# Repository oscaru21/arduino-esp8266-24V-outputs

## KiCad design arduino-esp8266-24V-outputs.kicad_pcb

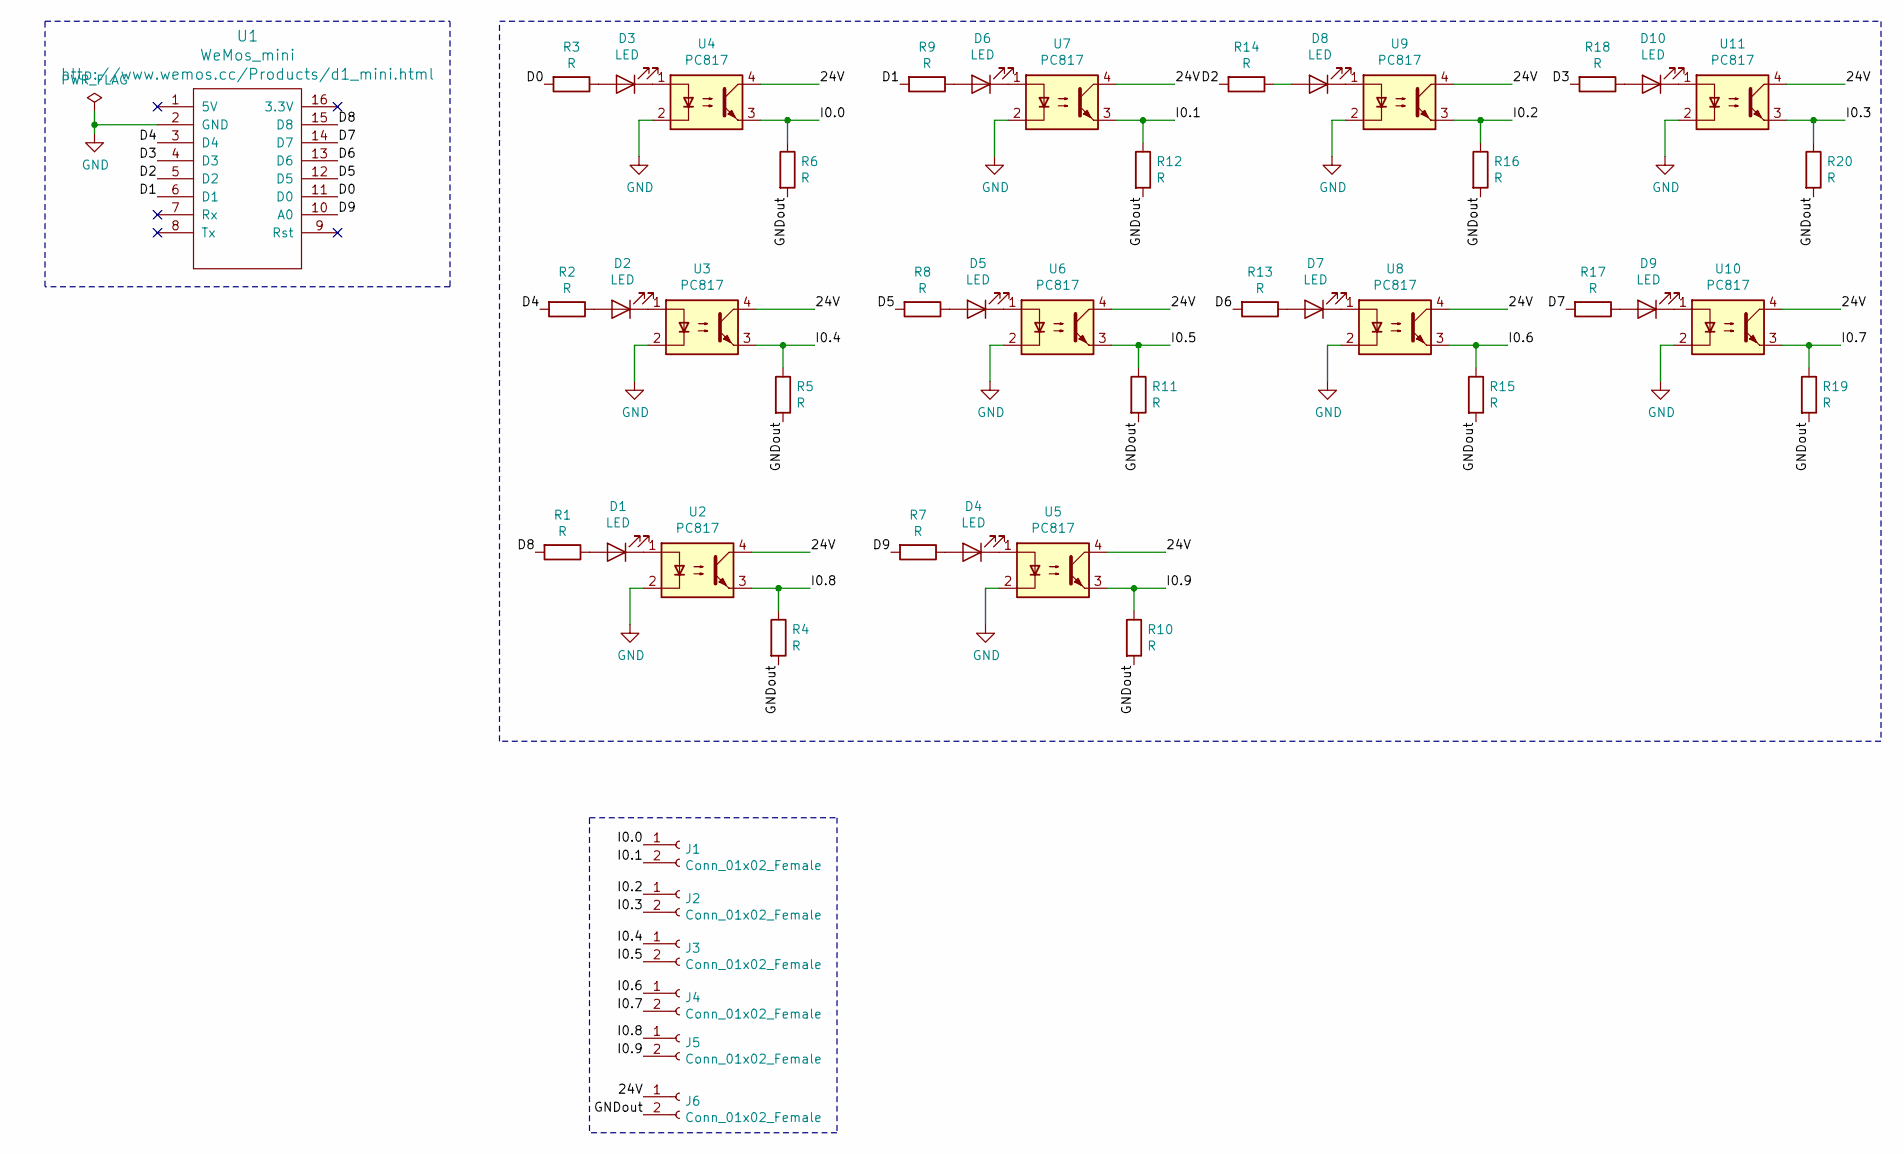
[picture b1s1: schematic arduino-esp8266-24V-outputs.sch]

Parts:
D1, D2, D3, D4, D5, D6, D7, D8, D9, D10: LED; LED_D3.0mm
J1, J2, J3, J4, J5, J6: Conn_01x02_Female; TerminalBlock_bornier-2_P5.08mm
R1, R2, R3, R4, R5, R6, R7, R8, R9, R10, R11, R12, R13, R14, R15, R16, R17, R18, R19, R20: R; R_Axial_DIN0207_L6.3mm_D2.5mm_P7.62mm_Horizontal
U1: WeMos_mini; wemos-d1-mini-with-pin-header-and-connector
U2, U3, U4, U5, U6, U7, U8, U9, U10, U11: PC817; DIP-4_W7.62mm

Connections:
/24V: J6.1, U2.4, U3.4, U4.4, U5.4, U6.4, U7.4, U8.4, U9.4, U10.4, U11.4
/D0: R3.2, U1.11 (D0)
/D1: R9.2, U1.6 (D1)
/D2: R14.2, U1.5 (D2)
/D3: R18.2, U1.4 (D3)
/D4: R2.2, U1.3 (D4)
/D5: R8.2, U1.12 (D5)
/D6: R13.2, U1.13 (D6)
/D7: R17.2, U1.14 (D7)
/D8: R1.2, U1.15 (D8)
/D9: R7.2, U1.10 (A0)
/GNDout: J6.2, R4.2, R5.2, R6.2, R10.2, R11.2, R12.2, R15.2, R16.2, R19.2, R20.2
/I0.0: J1.1, R6.1, U4.3
/I0.1: J1.2, R12.1, U7.3
/I0.2: J2.1, R16.1, U9.3
/I0.3: J2.2, R20.1, U11.3
/I0.4: J3.1, R5.1, U3.3
/I0.5: J3.2, R11.1, U6.3
/I0.6: J4.1, R15.1, U8.3
/I0.7: J4.2, R19.1, U10.3
/I0.8: J5.1, R4.1, U2.3
/I0.9: J5.2, R10.1, U5.3
GND: U1.2 (GND), U2.2, U3.2, U4.2, U5.2, U6.2, U7.2, U8.2, U9.2, U10.2, U11.2
unnamed: D1.1 (K), U2.1
unnamed: D1.2 (A), R1.1
unnamed: D2.1 (K), U3.1
unnamed: D2.2 (A), R2.1
unnamed: D3.1 (K), U4.1
unnamed: D3.2 (A), R3.1
unnamed: D4.1 (K), U5.1
unnamed: D4.2 (A), R7.1
unnamed: D5.1 (K), U6.1
unnamed: D5.2 (A), R8.1
unnamed: D6.1 (K), U7.1
unnamed: D6.2 (A), R9.1
unnamed: D7.1 (K), U8.1
unnamed: D7.2 (A), R13.1
unnamed: D8.1 (K), U9.1
unnamed: D8.2 (A), R14.1
unnamed: D9.1 (K), U10.1
unnamed: D9.2 (A), R17.1
unnamed: D10.1 (K), U11.1
unnamed: D10.2 (A), R18.1

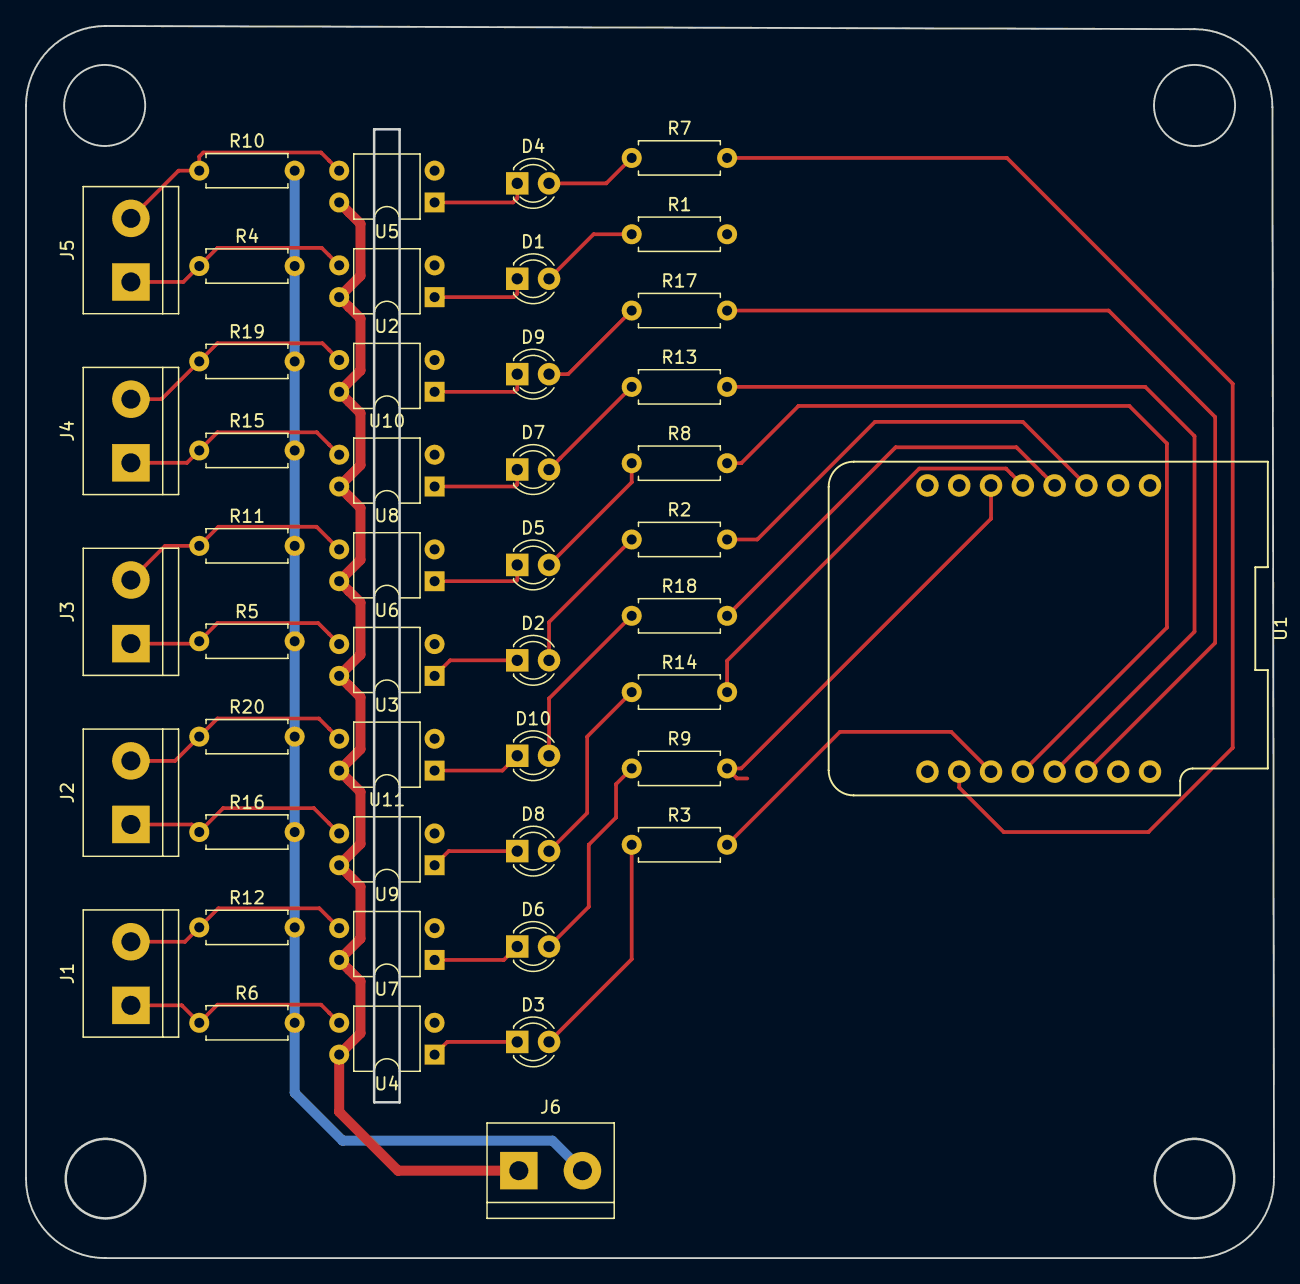
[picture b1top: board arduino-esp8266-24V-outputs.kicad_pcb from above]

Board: 2 copper layers, 99.7 x 98.4 mm, 47 parts (0 on the bottom side), 43 nets.

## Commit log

2020-08-16 add pcb layout
2020-08-17 finish tracks and layout
2020-08-17 add image
